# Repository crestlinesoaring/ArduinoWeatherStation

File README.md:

# ArduinoWeatherStation

Please check Wiki   
https://github.com/crestlinesoaring/ArduinoWeatherStation/wiki   

## Building with PlatformIO

This project is built with [PlatformIO](https://platformio.org) targeting the
Arduino Mega 2560 (`megaatmega2560`).

The third-party libraries are vendored directly under `libraries/` (no
submodules), so a fresh clone builds without any extra setup.

Build, upload, and monitor:

    pio run                  # build the mega firmware
    pio run -t upload        # upload to the board
    pio device monitor       # serial monitor (115200 baud)
    pio run -t upload -t monitor

A single `mega` env is defined in `platformio.ini`. Feature flags are
commented/uncommented in its `build_flags`:

    ANEMO_WS85                       WS85 ultrasonic anemometer on Serial1 (on by default)
    DONT_SLEEP                     skip night-time power save (on by default)
    BENCH_MODE                     stay awake, upload over Ethernet every 5 minutes
    ENABLE_HARDWARE_SIMULATION     enables the SIMULATE_* sensor fakes

The individual simulation `SIMULATE_RTC`, `SIMULATE_WIND_SPEED`,
`SIMULATE_WIND_DIRECTION`, `SIMULATE_INA219A_SOLAR_VOLTS`,
`SIMULATE_INA219A_SOLAR_MA`, `SIMULATE_INA219B_BATTERY_VOLTS`, and
`SIMULATE_INA219B_BATTERY_MA` defines are uncommented in the
HARDWARE SIMULATION SETTINGS block of `ArduinoWeatherStation.ino` (their
values describe the fake sensor readings: RTC Unix timestamp, wind speed in
mph, wind direction in ADC counts with 920 = North, solar/battery volts and mA).

These flags were formerly set inside the sketch (`#define` in pins.h and
ArduinoWeatherStation.ino); the feature toggles are now controlled from
`platformio.ini` build flags.

Pick the upload port explicitly with `--upload-port` when auto-detection fails:

    pio run -t upload --upload-port /dev/tty.usbmodem1101   # macOS
    pio run -t upload --upload-port COM3                    # Windows

PlatformIO merges the `.ino` files in `src/` into one sketch exactly like the
Arduino IDE (main file first, remaining files in alphabetical order), so all
globals and functions remain visible across files.

## Project layout

    src/            sketch sources (ArduinoWeatherStation.ino + tabs, pins.h, Marshall.h)
    libraries/      vendored third-party libraries, committed directly in the repo
    platformio.ini  build configuration (board, framework, library paths)

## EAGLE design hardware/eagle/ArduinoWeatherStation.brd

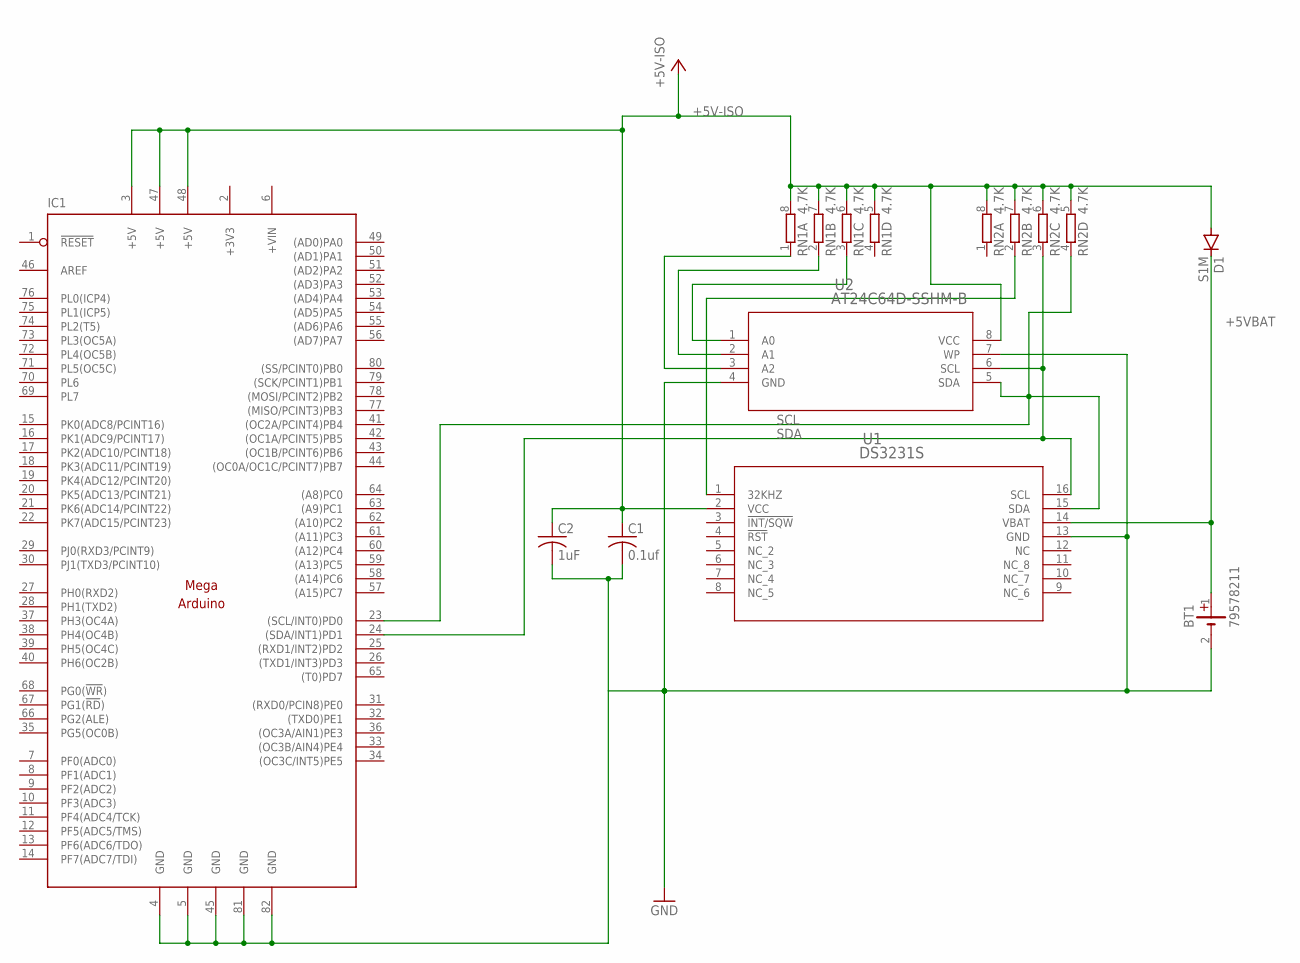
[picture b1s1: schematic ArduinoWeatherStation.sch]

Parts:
BT1: 79578211
C1: 0.1uf; C0603
C2: 1uF; C0603
D1: S1M; SMA
IC1: MEGAARDUINO_1; MEGA_ARDUINO
RN1, RN2: 4.7K; 0603-ARC
U1: DS3231S; 21-0042B_16
U2: AT24C64D-SSHM-B; 8S1

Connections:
+3V3: IC1.2 (+3V3)
+5V-ISO: C1.1, C2.1, D1.A, IC1.3 (+5V), IC1.47 (+5V), IC1.48 (+5V), RN1.5 (2), RN1.6 (2), RN1.7 (2), RN1.8 (2), RN2.5 (2), RN2.6 (2), RN2.7 (2), RN2.8 (2), U1.2 (VCC), U2.8 (VCC)
+5VBAT: BT1.1 (+), D1.C, U1.14 (VBAT)
+VIN: IC1.6 (+VIN)
GND-ISO: BT1.2 (-), C1.2, C2.2, IC1.4 (GND), IC1.5 (GND), IC1.45 (GND), IC1.81 (GND), IC1.82 (GND), U1.13 (GND), U2.4 (GND), U2.7 (WP)
unnamed: RN2.2 (1), U1.1 (32KHZ)
unnamed: RN1.3 (1), U2.1 (A0)
unnamed: RN1.2 (1), U2.2 (A1)
unnamed: RN1.1, U2.3 (A2)
SCL: IC1.23 ((SCL/INT0)PD0), RN2.4 (1), U1.15 (SDA), U2.5 (SDA)
SDA: IC1.24 ((SDA/INT1)PD1), RN2.3 (1), U1.16 (SCL), U2.6 (SCL)

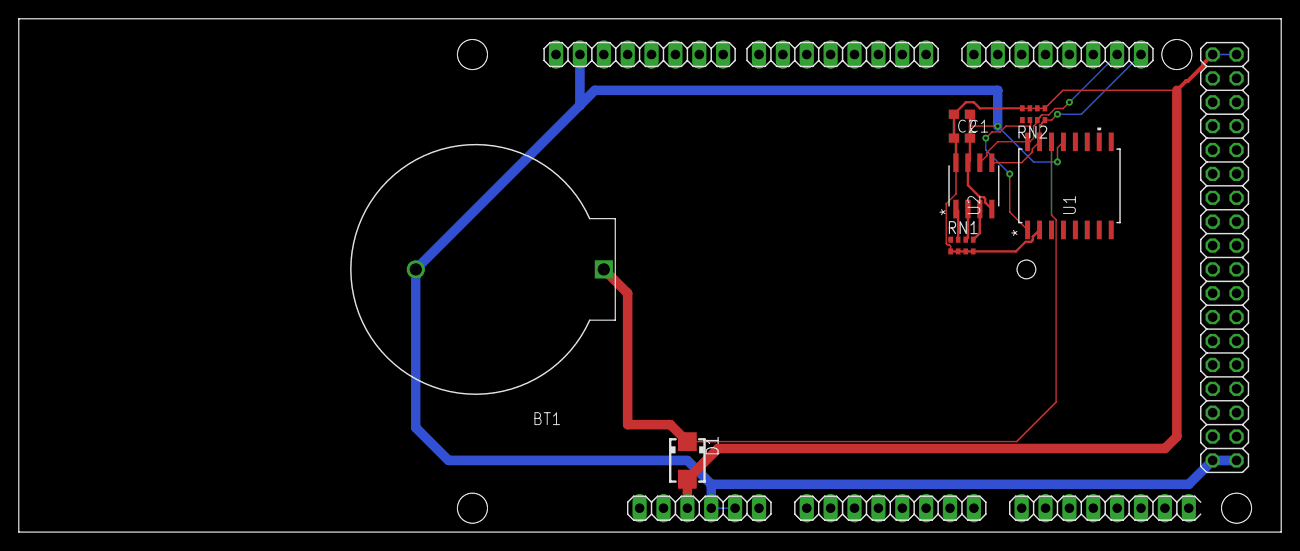
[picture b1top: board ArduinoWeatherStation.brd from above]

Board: 2 copper layers, 134.3 x 54.6 mm, 9 parts (0 on the bottom side), 9 nets.

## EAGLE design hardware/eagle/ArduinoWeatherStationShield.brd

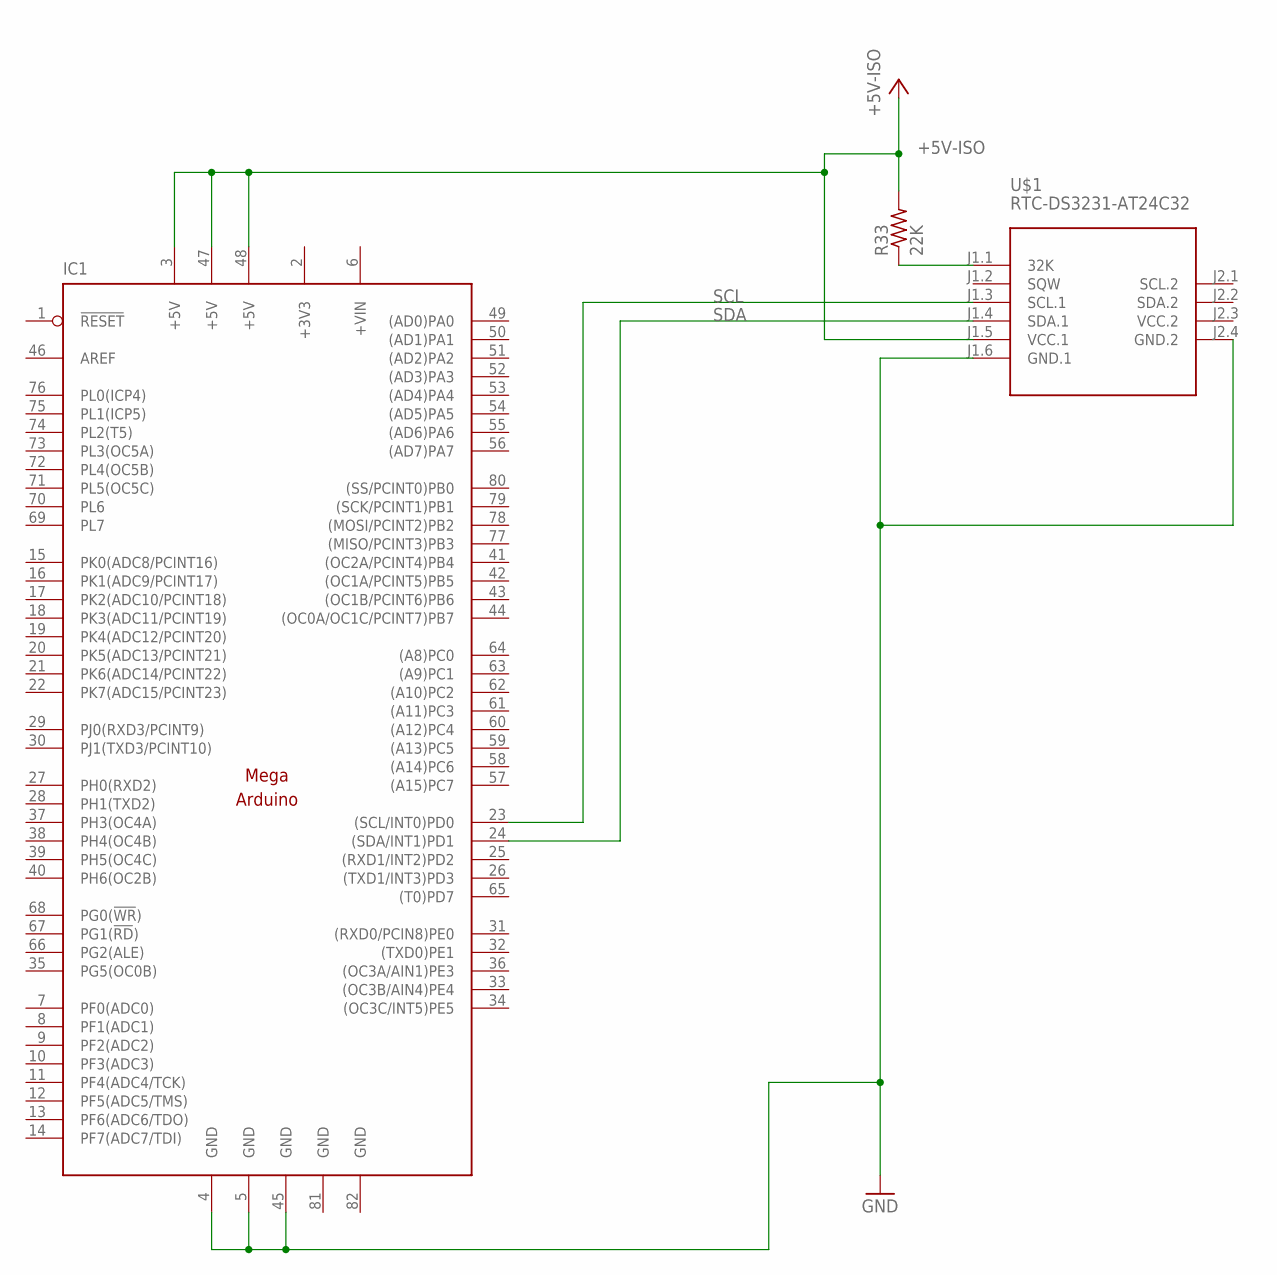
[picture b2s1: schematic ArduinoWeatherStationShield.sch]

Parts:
IC1: ARDUINO-MEGA-HEADER; MEGA_ARDUINO
R33: 22K; R0402
U$1: RTC-DS3231-AT24C32

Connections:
+3V3: IC1.2 (+3V3)
+5V-ISO: IC1.3 (+5V), IC1.47 (+5V), IC1.48 (+5V), R33.2, U$1.J1.5 (VCC.1)
+VIN: IC1.6 (+VIN)
GND-ISO: IC1.4 (GND), IC1.5 (GND), IC1.45 (GND), IC1.81 (GND), IC1.82 (GND), U$1.J1.6 (GND.1), U$1.J2.4 (GND.2)
unnamed: R33.1, U$1.J1.1 (32K)
SCL: IC1.23 ((SCL/INT0)PD0), U$1.J1.3 (SCL.1)
SDA: IC1.24 ((SDA/INT1)PD1), U$1.J1.4 (SDA.1)
VCC.2: U$1.J2.3 (VCC.2)

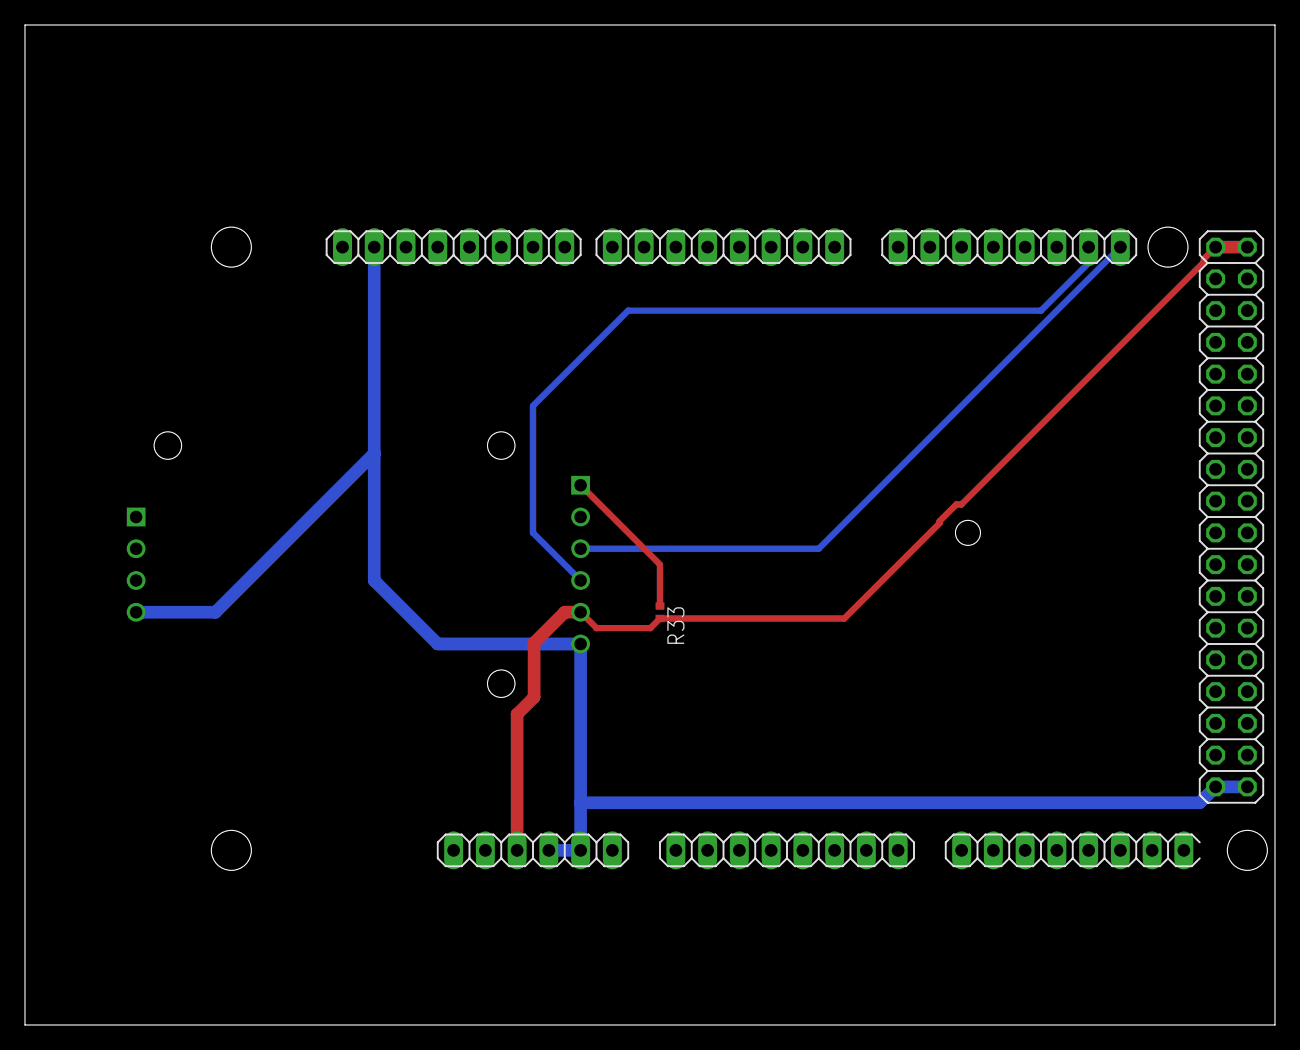
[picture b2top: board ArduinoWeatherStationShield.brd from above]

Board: 2 copper layers, 100.0 x 80.0 mm, 3 parts (1 on the bottom side), 5 nets.

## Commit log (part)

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2017-09-14 Added library links, .gitignore
2017-09-14 Added initial interpretation of Fritzing diagram
2017-09-14 Added Ubiquiti
2017-09-15 Added first tracked version of main sketch
    Sensitive information factored out into Marshall.h, not included in repository
2017-09-15 Changed Ubiquiti and Eth power control pins to constants
2017-09-15 Abstracted Ethernet disable/enable into methods
2017-09-15 Replaced all tabs and standardized indents to 2 spaces
2017-09-16 Solar Panel shutoff > 350ma, read both BME280s, etc..
    Added Jimmy's improved setup() ethernet disable/enable routine, sets MISO/MOSI to input I think
    Some small formatting changes too.
2017-09-18 Added corrections from discussion with Jimmy
2017-09-18 Added first draft of power management for issue #3
    Also removed IP constants duplicated in Marshall.h, changed first-time boot to use enableEthernet() and disableEthernet()
2017-09-19 Day/night every 4 minutes with #define FOURMINUTEDAY
    So that Jimmy can test day/night transition, switch every 4 minutes instead of sticking to the sunrise/sunset schedule.
2017-09-19 Now 6 minute days, no wdt reset on day, ethernet.begin() added to enableEthernet()
2017-09-21 Added crazy temperature correction for wind direction
    Also added Visual Studio project & solution files
2017-09-22 Added FakeWebServer tool
2017-09-27 INA219a MMA, some cosmetic fixes
2017-09-28 Cosmetic fixes, formatting.
    A few fixes to make:
    pending, added time output for better diagnostics: Double-check 5 minute solar panel timeout, seems not to last 5 minutes?
    --done (hopefully). Fix formatting for negative numbers (000-77)
    --done. Serial output of what time solar is disabled/enabled
    --done. Multiply both INA readings by 2 (350mA -> 700mA)
    --done. reset count of ina readings to zero each minute. Note it gets about 4,200 readings per minute.
2017-09-30 Fix endless loop in enableEthernet()
    The 30 second pause caused endless looping if a minute rollover happened during that pause, because everything happens when each minute rolls over. Fixed by not running enableEthernet() every minute.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
2017-09-30 Report solar panel cutoff charging rate
2017-10-03 web server for initiating reboot
    First draft of a web server. It's not good at all, but it seems to work.
2017-10-15 1h before sunrise, small formatting, ina smoothing
2017-10-31 19a, Untested! Power save, 2/10 upload when cloudy
    If the battery mA reading is -50 or lower, then go into "night" mode for minute 2-9 of every 10 minutes. Turns on for 2 minutes, because it can take until the next minute for the U to be ready to tra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
2017-11-01 Remove <300mA eth cutoff; wasn't working
    Some mild power saving if voltage gets too low.
2017-12-05 SD card archive. v.19i
    Archives data to SD card. Still does not send any cached data to the website, but getting close to that.
    Some light logging on WatchDog resets. Mild code cleanup and logic improvements.
2017-12-08 19o, send once every 5 minutes
    Improved Ubiquiti enable/disable, new pin architecture (for Brain2).
    Saves up data for 5 minutes, and sends in a batch. No error checking really, and sometimes uploads end up out-of-order. It's not refined yet.
2018-02-23 20t, minor cleanup, more telnet commands
    Lots of commands and options. Mostly prep for adding cameras, just debug stuff.
2018-06-01 ver 20x7, minor interrupt counting on pins 18 & 19
2018-09-07 21f; cam control, more telnet commands
    Allow cameras to stay on through reboots by saving their state to eeprom, added "sleep / wake" before / after sunset time to eeprom & telnet so it can be adjusted without uploading a new version. As 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
2018-09-14 v. 21j, bugfixes, more telnet commands
2018-10-07 21r, basic camera functionality
    Turns cameras on when voltage is high enough, turns them off when running negative too long or voltage gets too low.
    Beginnings of "snapshot request" functionality, but it doesn't actually work yet. The auto-off is so aggressive, we can't keep the cameras on long enough to get manual early-morning or late-evening s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
2019-01-08 Added missing SdFat submodule to libraries folder.
2019-01-10 Add Forked Adafruit_INA219 submodule
2019-01-10 .21t, broken snapshot feature and rename cameras
2019-01-24 Fix low hanging compiler warnings.
2019-04-08 .21v, cameras only after 5 mins charging
2019-04-12 .21w, fix mistakes from .21v
2019-08-25 -Library updates - RTC initialization without Ethernet - JSON Serial Parser
2019-09-16 Command Parser, time and weather save
2019-09-17 weather storing to eeprom

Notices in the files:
parts and their libraries:
diy-modules: Released under the Creative Commons Attribution 4.0 International License: http://creativecommons.org/licenses/by/4.0
